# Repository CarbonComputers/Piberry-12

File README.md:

## PiBerry v12 – Final Iteration

**PiBerry v12** marks the final and most refined revision of the PiBerry handheld Linux terminal. Designed with both form and function in mind, this version brings together the best elements of previous iterations while introducing a more polished aesthetic, improved usability, and support for premium display hardware.

### 🔧 What's New in v12:

* **Refined Aesthetic Design**
  Complete overhaul of the external design for a cleaner, more modern look. Every detail has been revisited to ensure a visually cohesive and ergonomic form factor.
  Keyboard connectivity is simpler as it's driven via USB instead of I2C, you only have to flash the firmware and install the display drivers.

* **HyperPixel 4.0" Display Support**
  Now compatible with the high-resolution **HyperPixel 4.0" touchscreen**, offering a sharper, more responsive interface for your Linux workflows, tools, and custom interfaces, drivers are baked into Pi OS, and many others.
  Waveshare or other 3.5" displays are still compatible, make sure you use the right 3D file

* **Community & Collaboration**
  This final version wouldn’t have been possible without the support and insights of the amazing open-source and hardware community. Special thanks to all contributors, testers, and developers who offered feedback and improvements throughout the PiBerry journey.

### 🔍 Overview:

* Fully integrated handheld Linux device
* Designed around the Raspberry Pi Zero 2W (possibly a CM4 - with a mini carrier)
* Optimized for penetration testing, system diagnostics, portable dev environments, and retro computing/ gaming
* Runs your choice of Linux (Kali, Raspberry Pi OS, etc.)
* Powered by an onboard battery with safe shutdown and charging logic
* Support for keyboards, touch navigation, and peripheral integration with the BBQ20

---

PiBerry v12 is a culmination of passion, learning, and iteration — a celebration of community-powered hardware.

We hope you enjoy building and using it as much as we enjoyed bringing it to life.

Get yours or find out more about the latest builds at [Carbon Computers](https://carboncomputers.us)

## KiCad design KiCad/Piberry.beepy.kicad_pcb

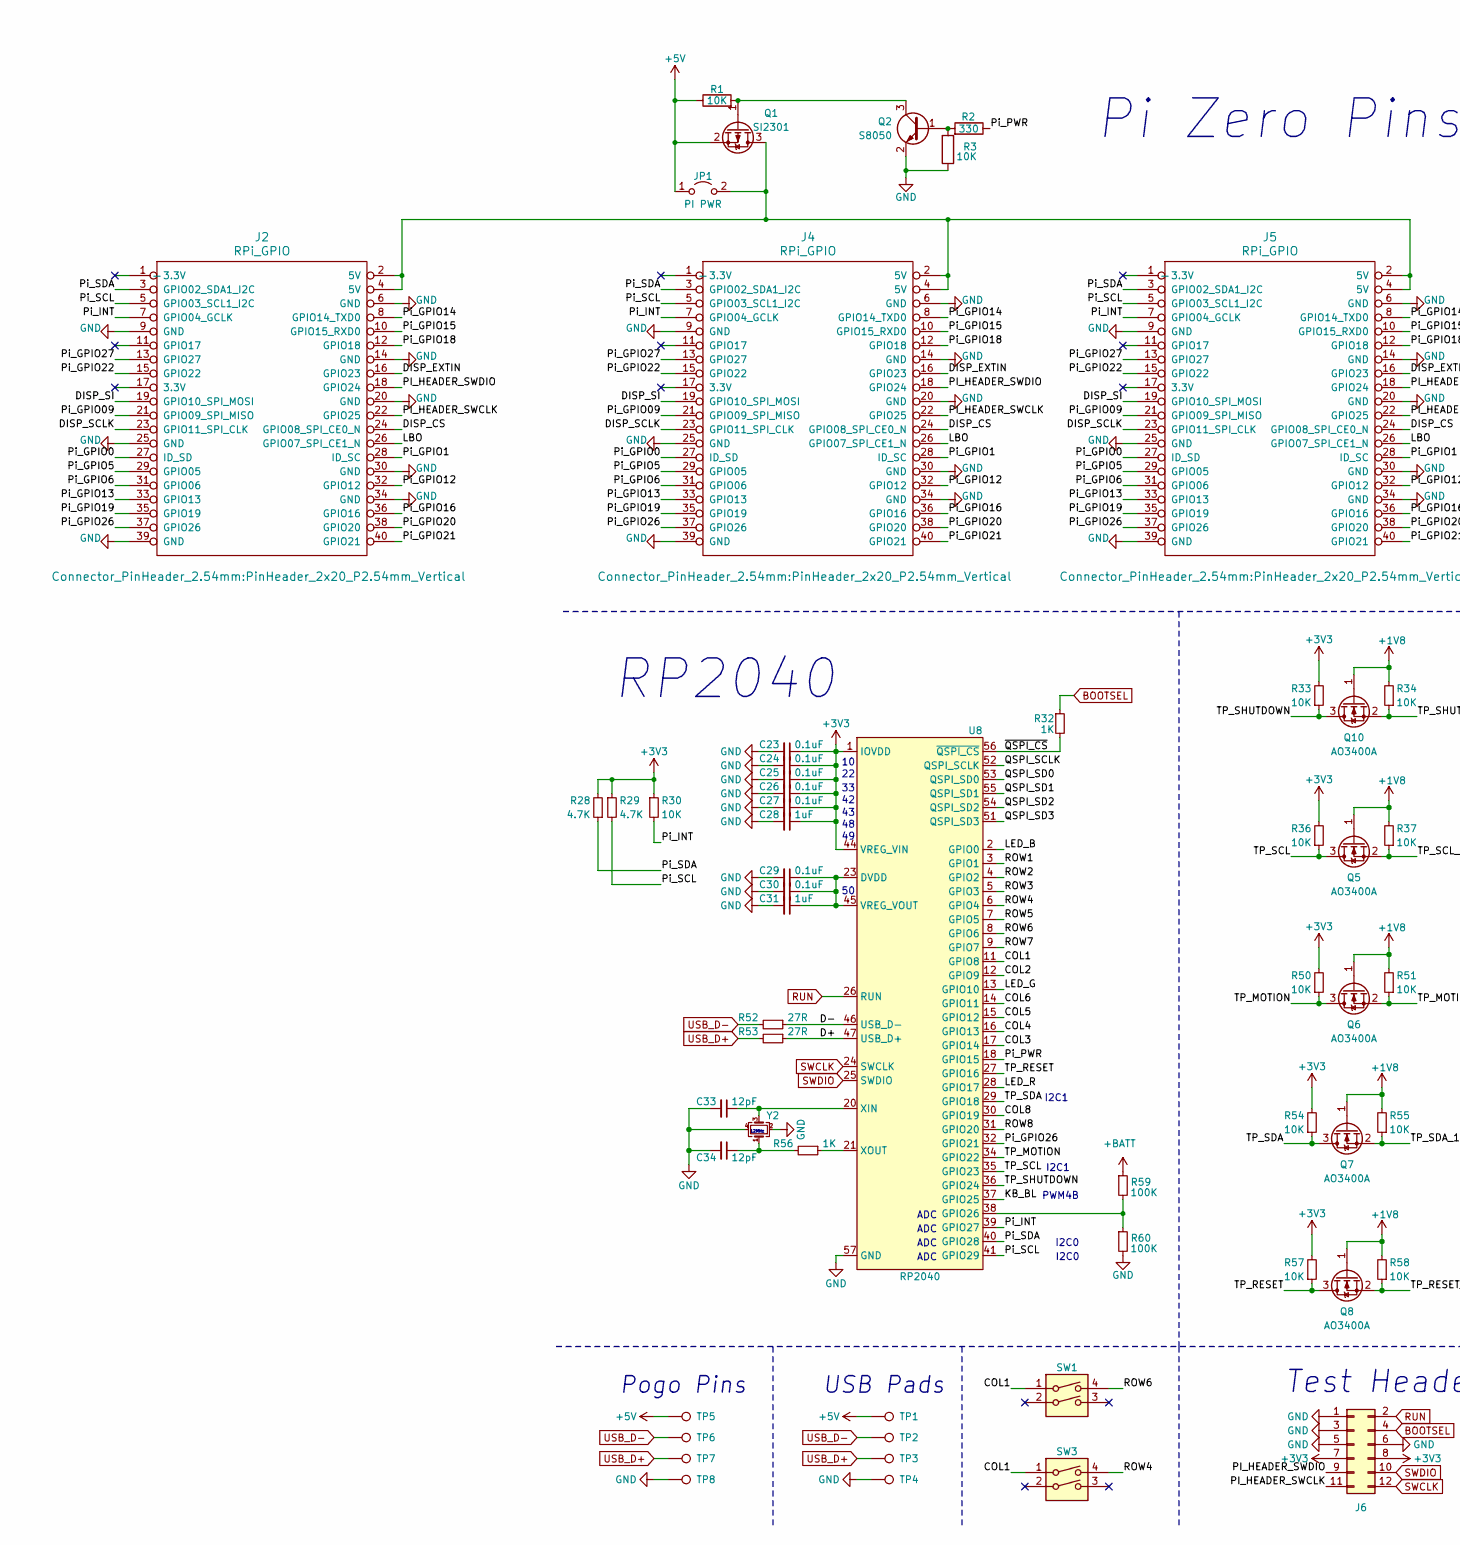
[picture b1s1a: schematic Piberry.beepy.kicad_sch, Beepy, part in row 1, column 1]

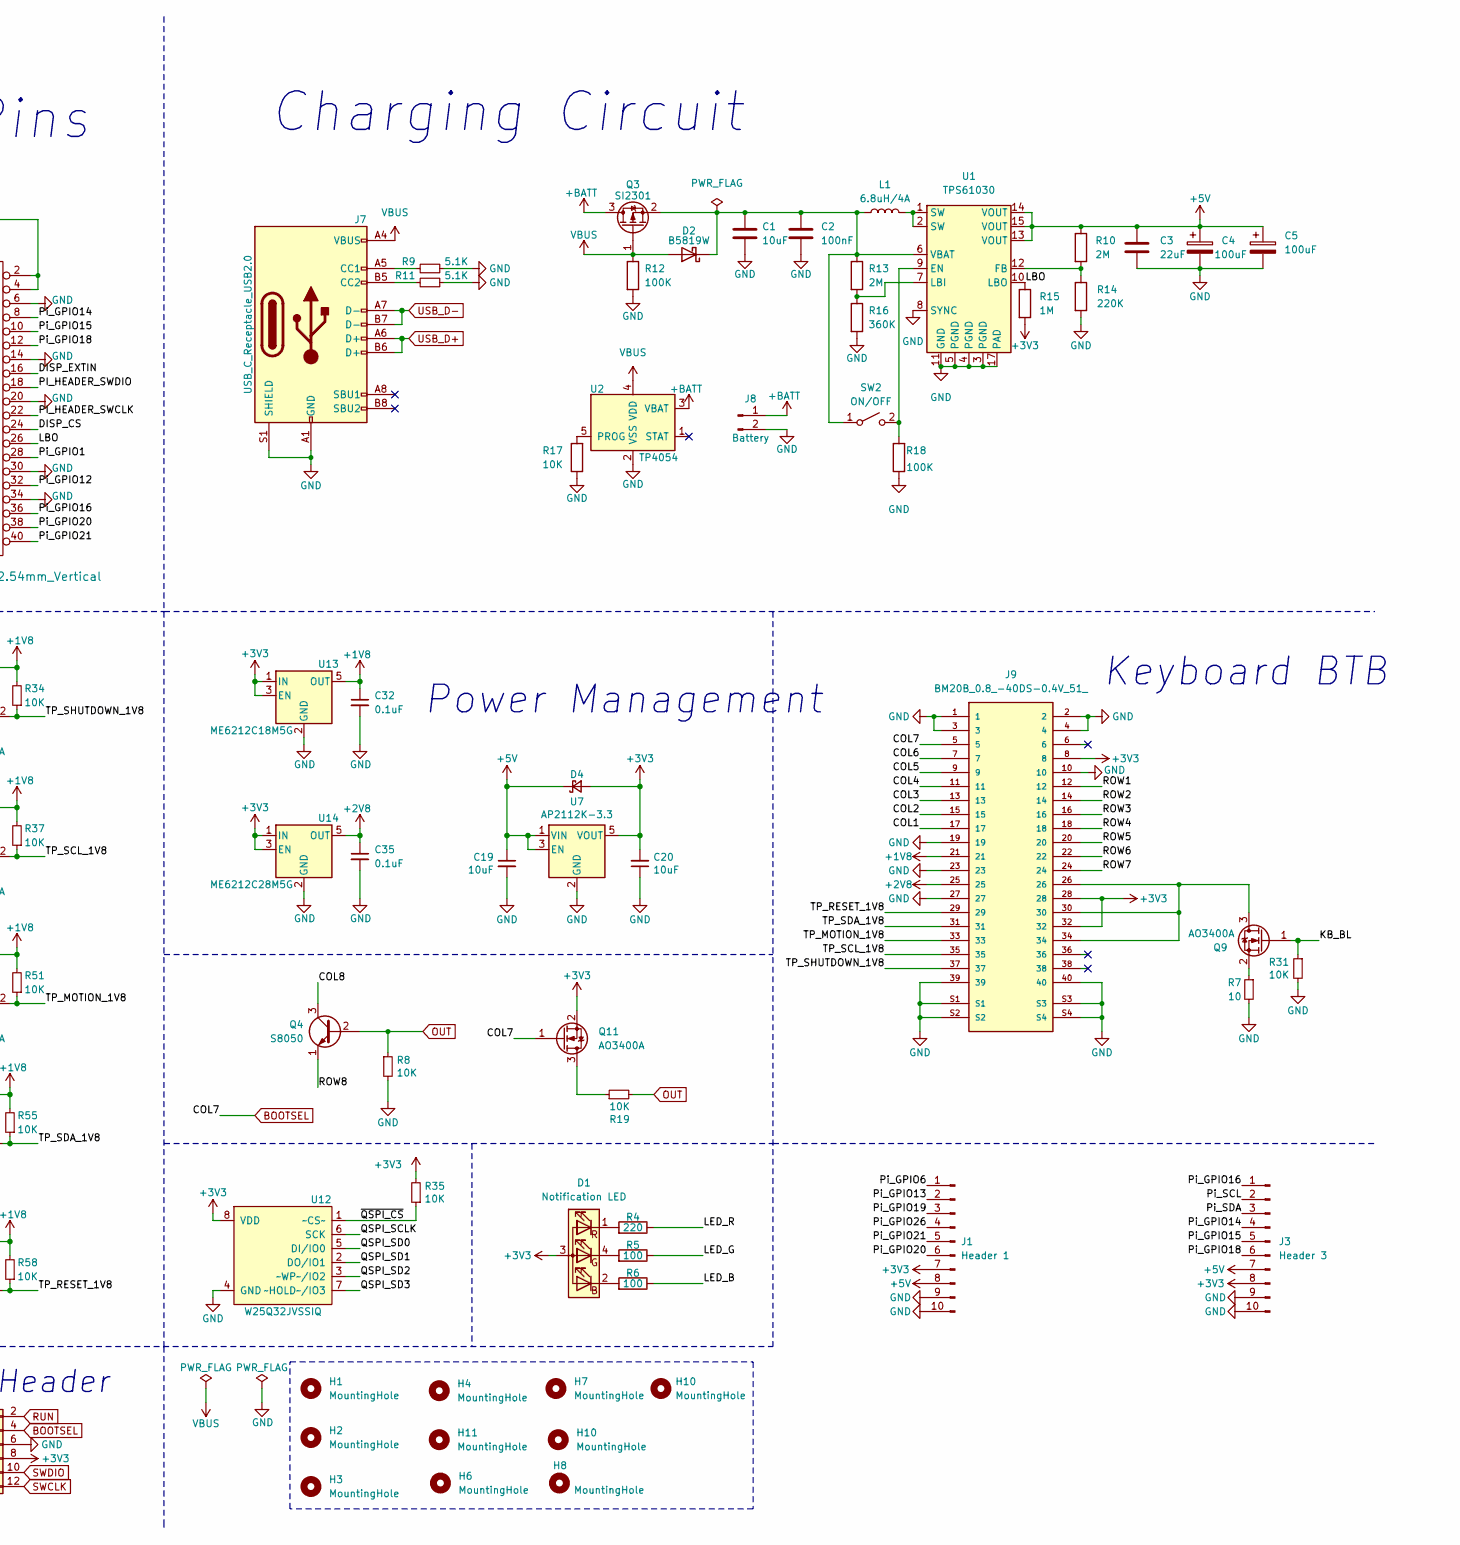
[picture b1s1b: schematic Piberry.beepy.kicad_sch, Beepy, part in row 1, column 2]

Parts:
C1, C19, C20: 10uF; C_0603_1608Metric; LCSC C96446
C2: 100nF; C_0603_1608Metric; LCSC C14663
C3: 22uF; C_1206_3216Metric; LCSC C12891
C4, C5: 100uF; CP_EIA-3528-15_AVX-H; LCSC C129289
C23, C24, C25, C26, C27, C29, C30, C32, C35: 0.1uF; C_0603_1608Metric; LCSC C14663
C28, C31: 1uF; C_0603_1608Metric; LCSC C15849
C33, C34: 12pF; C_0603_1608Metric; LCSC C38523
D1: Notification LED; FM-B2020RGBA-HG; LCSC C108793
D2: B5819W; D_SOD-123; LCSC C64885
D4: D_Schottky_Small; D_SOD-323; LCSC C114023
H1, H4, H7, H10: MountingHole; MountingHole_2.2mm_M2
H2, H3, H6, H11: MountingHole; MountingHole_2.5mm
H8: MountingHole; MountingHole_2.7mm_M2.5
J1: Header 1; PinHeader_1x10_P2.54mm_Vertical; LCSC C57369
J2, J4, J5: RPi_GPIO; PinHeader_2x20_P2.54mm_Vertical
J3: Header 3; PinHeader_1x10_P2.54mm_Vertical; LCSC C57369
J6: PRG_HEADER; PinHeader_2x06_P1.27mm_Vertical_SMD
J7: USB_C_Receptacle_USB2.0; USB_C_Receptacle_HRO_TYPE-C-31-M-12; LCSC C165948
J8: Battery; JST_PH_S2B-PH-SM4-TB_1x02-1MP_P2.00mm_Horizontal; LCSC C295747
J9: BM20B_0.8_-40DS-0.4V_51_; HRS_BM20B_0.8_-40DS-0.4V_51_; LCSC C424543
JP1: PI PWR; SolderJumper-2_P1.3mm_Open_RoundedPad1.0x1.5mm
L1: 6.8uH/4A; L_Bourns_SRP7028A_7.3x6.6mm; LCSC C497879
Q1, Q3: SI2301; SOT-23; LCSC C2891731
Q2, Q4: S8050; SOT-23; LCSC C916390
Q5, Q6, Q7, Q8, Q9, Q10, Q11: AO3400A; SOT-23; LCSC C20917
R1, R3, R8, R17, R19, R30, R31, R33, R34, R35, R36, R37, R50, R51, R54, R55, R57, R58: 10K; R_0603_1608Metric; LCSC C25804
R2: 330; R_0603_1608Metric; LCSC C23138
R4: 220; R_0603_1608Metric; LCSC C22962
R5, R6: 100; R_0603_1608Metric; LCSC C22775
R7: 10; R_0603_1608Metric; LCSC C22859
R9, R11: 5.1K; R_0603_1608Metric; LCSC C23186
R10, R13: 2M; R_0603_1608Metric; LCSC C22976
R12, R18, R59, R60: 100K; R_0603_1608Metric; LCSC C25803
R14: 220K; R_0603_1608Metric; LCSC C22961
R15: 1M; R_0603_1608Metric; LCSC C22935
R16: 360K; R_0603_1608Metric; LCSC C23146
R28, R29: 4.7K; R_0603_1608Metric; LCSC C23162
R32, R56: 1K; R_0603_1608Metric; LCSC C21190
R52, R53: 27R; R_0603_1608Metric; LCSC C403464
SW1, SW3: SW_DIP_x02; GT-TC018X; LCSC C963235
SW2: ON/OFF; SW_SPDT_PCM12; LCSC C963206
TP1, TP2, TP3, TP4: TestPoint; TestPoint_Pad_1.5x1.5mm
TP5, TP8: TestPoint; TestPoint_THTPad_D2.0mm_Drill1.0mm
TP6, TP7: TestPoint; TestPoint_THTPad_D1.5mm_Drill0.7mm
U1: TPS61030; HTSSOP-16-1EP_4.4x5mm_P0.65mm_EP3.4x5mm_Mask2.46x2.31mm_The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; LCSC C9842
U2: TP4054; SOT-23-5; LCSC C668215
U7: AP2112K-3.3; SOT-23-5; LCSC C51118
U8: RP2040; QFN-56-1EP_7x7mm_P0.4mm_EP5.6x5.6mm; LCSC C2040
U12: W25Q32JVSSIQ; SSOP-8_5.25x5.24mm_P1.27mm; LCSC C82344
U13: ME6212C18M5G; SOT-23-5; LCSC C236669
U14: ME6212C28M5G; SOT-23-5; LCSC C427596
Y2: XYDBPCNANF-12MHZ; Crystal_SMD_3225-4Pin_3.2x2.5mm; LCSC C284155

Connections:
+1V8: C32.1, J9.21, Q5.1 (G), Q6.1 (G), Q7.1 (G), Q8.1 (G), Q10.1 (G), R34.2, R37.2, R51.2, R55.2, R58.2, U13.5 (OUT)
+2V8: C35.1, J9.25, U14.5 (OUT)
+3V3: C20.2, C23.1, C24.1, C25.1, C26.1, C27.1, C28.1, D1.3 (A), D4.2 (A), J1.7, J3.8, J6.7, J6.8, J9.8, J9.28, J9.32, Q11.2 (S), R15.2, R28.2, R29.1, R30.1, R33.2, R35.2, R36.2, R50.2, R54.2, R57.2, U7.5 (VOUT), U8.1 (IOVDD), U8.10 (IOVDD), U8.22 (IOVDD), U8.33 (IOVDD), U8.42 (IOVDD), U8.43 (ADC_AVDD), U8.44 (VREG_VIN), U8.48 (USB_VDD), U8.49 (IOVDD), U12.8 (VDD), U13.1 (IN), U13.3 (EN), U14.1 (IN), U14.3 (EN)
+5V: C3.1, C4.1, C5.1, C19.1, D4.1 (K), J1.8, J3.7, JP1.1 (A), Q1.2 (S), R1.1, R10.1, TP1.1, TP5.1, U1.13 (VOUT), U1.14 (VOUT), U1.15 (VOUT), U7.1 (VIN), U7.3 (EN)
+BATT: J8.1, Q3.3 (D), R59.1, U2.3 (VBAT)
/COL1: J9.17, SW1.1, SW3.1, U8.11 (GPIO8)
/COL2: J9.15, U8.12 (GPIO9)
/COL3: J9.13, U8.17 (GPIO14)
/COL4: J9.11, U8.16 (GPIO13)
/COL5: J9.9, U8.15 (GPIO12)
/COL6: J9.7, U8.14 (GPIO11)
/COL8: Q4.3 (C), U8.30 (GPIO19)
/D+: R53.1, U8.47 (USB_D+)
/D-: R52.1, U8.46 (USB_D-)
/DISP_CS: J2.24 (GPIO08_SPI_CE0_N), J4.24 (GPIO08_SPI_CE0_N), J5.24 (GPIO08_SPI_CE0_N)
/DISP_EXTIN: J2.16 (GPIO23), J4.16 (GPIO23), J5.16 (GPIO23)
/DISP_SCLK: J2.23 (GPIO11_SPI_CLK), J4.23 (GPIO11_SPI_CLK), J5.23 (GPIO11_SPI_CLK)
/DISP_SI: J2.19 (GPIO10_SPI_MOSI), J4.19 (GPIO10_SPI_MOSI), J5.19 (GPIO10_SPI_MOSI)
/KB_BL: Q9.1 (G), R31.1, U8.37 (GPIO25)
/LBO: J2.26 (GPIO07_SPI_CE1_N), J4.26 (GPIO07_SPI_CE1_N), J5.26 (GPIO07_SPI_CE1_N), R15.1, U1.10 (LBO)
/LED_B: R6.1, U8.2 (GPIO0)
/LED_G: R5.1, U8.13 (GPIO10)
/LED_R: R4.1, U8.28 (GPIO17)
/PI_HEADER_SWCLK: J2.22 (GPIO25), J4.22 (GPIO25), J5.22 (GPIO25), J6.11
/PI_HEADER_SWDIO: J2.18 (GPIO24), J4.18 (GPIO24), J5.18 (GPIO24), J6.9
/Pi_GPIO0: J2.27 (ID_SD), J4.27 (ID_SD), J5.27 (ID_SD)
/Pi_GPIO1: J2.28 (ID_SC), J4.28 (ID_SC), J5.28 (ID_SC)
/Pi_GPIO5: J2.29 (GPIO05), J4.29 (GPIO05), J5.29 (GPIO05)
/Pi_GPIO6: J1.1, J2.31 (GPIO06), J4.31 (GPIO06), J5.31 (GPIO06)
/Pi_GPIO09: J2.21 (GPIO09_SPI_MISO), J4.21 (GPIO09_SPI_MISO), J5.21 (GPIO09_SPI_MISO)
/Pi_GPIO12: J2.32 (GPIO12), J4.32 (GPIO12), J5.32 (GPIO12)
/Pi_GPIO13: J1.2, J2.33 (GPIO13), J4.33 (GPIO13), J5.33 (GPIO13)
/Pi_GPIO14: J2.8 (GPIO14_TXD0), J3.4, J4.8 (GPIO14_TXD0), J5.8 (GPIO14_TXD0)
/Pi_GPIO15: J2.10 (GPIO15_RXD0), J3.5, J4.10 (GPIO15_RXD0), J5.10 (GPIO15_RXD0)
/Pi_GPIO16: J2.36 (GPIO16), J3.1, J4.36 (GPIO16), J5.36 (GPIO16)
/Pi_GPIO18: J2.12 (GPIO18), J3.6, J4.12 (GPIO18), J5.12 (GPIO18)
/Pi_GPIO19: J1.3, J2.35 (GPIO19), J4.35 (GPIO19), J5.35 (GPIO19)
/Pi_GPIO20: J1.6, J2.38 (GPIO20), J4.38 (GPIO20), J5.38 (GPIO20)
/Pi_GPIO21: J1.5, J2.40 (GPIO21), J4.40 (GPIO21), J5.40 (GPIO21)
/Pi_GPIO22: J2.15 (GPIO22), J4.15 (GPIO22), J5.15 (GPIO22)
/Pi_GPIO26: J1.4, J2.37 (GPIO26), J4.37 (GPIO26), J5.37 (GPIO26), U8.32 (GPIO21)
/Pi_GPIO27: J2.13 (GPIO27), J4.13 (GPIO27), J5.13 (GPIO27)
/Pi_INT: J2.7 (GPIO04_GCLK), J4.7 (GPIO04_GCLK), J5.7 (GPIO04_GCLK), R30.2, U8.39 (GPIO27)
/Pi_PWR: R2.1, U8.18 (GPIO15)
/Pi_SCL: J2.5 (GPIO03_SCL1_I2C), J3.2, J4.5 (GPIO03_SCL1_I2C), J5.5 (GPIO03_SCL1_I2C), R29.2, U8.41 (GPIO29)
/Pi_SDA: J2.3 (GPIO02_SDA1_I2C), J3.3, J4.3 (GPIO02_SDA1_I2C), J5.3 (GPIO02_SDA1_I2C), R28.1, U8.40 (GPIO28)
/QSPI_SCLK: U8.52 (QSPI_SCLK), U12.6 (SCK)
/QSPI_SD0: U8.53 (QSPI_SD0), U12.5 (DI/IO0)
/QSPI_SD1: U8.55 (QSPI_SD1), U12.2 (DO/IO1)
/QSPI_SD2: U8.54 (QSPI_SD2), U12.3 (~WP~/IO2)
/QSPI_SD3: U8.51 (QSPI_SD3), U12.7 (~HOLD~/IO3)
/ROW1: J9.12, U8.3 (GPIO1)
/ROW2: J9.14, U8.4 (GPIO2)
/ROW3: J9.16, U8.5 (GPIO3)
/ROW4: J9.18, SW3.4, U8.6 (GPIO4)
/ROW5: J9.20, U8.7 (GPIO5)
/ROW6: J9.22, SW1.4, U8.8 (GPIO6)
/ROW7: J9.24, U8.9 (GPIO7)
/ROW8: Q4.1 (E), U8.31 (GPIO20)
/TP_MOTION: Q6.3 (D), R50.1, U8.34 (GPIO22)
/TP_MOTION_1V8: J9.33, Q6.2 (S), R51.1
/TP_RESET: Q8.3 (D), R57.1, U8.27 (GPIO16)
/TP_RESET_1V8: J9.29, Q8.2 (S), R58.1
/TP_SCL: Q5.3 (D), R36.1, U8.35 (GPIO23)
/TP_SCL_1V8: J9.35, Q5.2 (S), R37.1
/TP_SDA: Q7.3 (D), R54.1, U8.29 (GPIO18)
/TP_SDA_1V8: J9.31, Q7.2 (S), R55.1
/TP_SHUTDOWN: Q10.3 (D), R33.1, U8.36 (GPIO24)
/TP_SHUTDOWN_1V8: J9.37, Q10.2 (S), R34.1
/~QSPI_CS: R32.2, R35.1, U8.56 (~QSPI_CS), U12.1 (~CS~)
BOOTSEL: J6.4, J9.5, Q11.1 (G), R32.1
GND: C1.2, C2.2, C3.2, C4.2, C5.2, C19.2, C20.1, C23.2, C24.2, C25.2, C26.2, C27.2, C28.2, C29.2, C30.2, C31.2, C32.2, C33.2, C34.2, C35.2, J1.9, J1.10, J2.6 (GND), J2.9 (GND), J2.14 (GND), J2.20 (GND), J2.25 (GND), J2.30 (GND), J2.34 (GND), J2.39 (GND), J3.9, J3.10, J4.6 (GND), J4.9 (GND), J4.14 (GND), J4.20 (GND), J4.25 (GND), J4.30 (GND), J4.34 (GND), J4.39 (GND), J5.6 (GND), J5.9 (GND), J5.14 (GND), J5.20 (GND), J5.25 (GND), J5.30 (GND), J5.34 (GND), J5.39 (GND), J6.1, J6.3, J6.5, J6.6, J7.A1 (GND), J7.A12 (GND), J7.B1 (GND), J7.B12 (GND), J7.S1 (SHIELD), J8.2, J9.1, J9.2, J9.3, J9.4, J9.10, J9.19, J9.23, J9.27, J9.39, J9.40, J9.S1, J9.S2, J9.S3, J9.S4, Q2.2 (E), R3.1, R7.2, R8.2, R9.1, R11.1, R12.2, R14.2, R16.2, R17.1, R18.1, R31.2, R60.2, TP4.1, TP8.1, U1.3 (PGND), U1.4 (PGND), U1.5 (PGND), U1.8 (SYNC), U1.11 (GND), U1.17 (PAD), U2.2 (VSS), U7.2 (GND), U8.19 (TESTEN), U8.57 (GND), U12.4 (GND), U12.9 (GND), U13.2 (GND), U14.2 (GND), Y2.2, Y2.4
unnamed: C34.1, R56.2, Y2.1
unnamed: D1.2 (BK), R6.2
unnamed: D1.4 (GK), R5.2
unnamed: D1.1 (RK), R4.2
unnamed: C1.1, C2.1, D2.1 (K), L1.1, Q3.2 (S), R13.1, SW2.1 (A), U1.6 (VBAT)
unnamed: J7.A5 (CC1), R9.2
unnamed: J7.B5 (CC2), R11.2
unnamed: J2.2 (5V), J2.4 (5V), J4.2 (5V), J4.4 (5V), J5.2 (5V), J5.4 (5V), JP1.2 (B), Q1.3 (D)
unnamed: L1.2, U1.1 (SW), U1.2 (SW)
unnamed: Q1.1 (G), Q2.3 (C), R1.2
unnamed: Q2.1 (B), R2.2, R3.2
unnamed: J9.26, J9.30, J9.34, Q9.3 (D)
unnamed: Q9.2 (S), R7.1
unnamed: Q11.3 (D), R19.1
unnamed: R18.2, SW2.2 (B), U1.9 (EN)
unnamed: R10.2, R14.1, U1.12 (FB)
unnamed: R13.2, R16.1, U1.7 (LBI)
unnamed: R17.2, U2.5 (PROG)
unnamed: R59.2, R60.1, U8.38 (GPIO26)
unnamed: C29.1, C30.1, C31.1, U8.23 (DVDD), U8.45 (VREG_VOUT), U8.50 (DVDD)
unnamed: C33.1, U8.20 (XIN), Y2.3
unnamed: R56.1, U8.21 (XOUT)
OUT: Q4.2 (B), R8.1, R19.2
RUN: J6.2, U8.26 (RUN)
SWCLK: J6.12, U8.24 (SWCLK)
SWDIO: J6.10, U8.25 (SWDIO)
USB_D+: J7.A6 (D+), J7.B6 (D+), R53.2, TP3.1, TP7.1
USB_D-: J7.A7 (D-), J7.B7 (D-), R52.2, TP2.1, TP6.1
VBUS: D2.2 (A), J7.A4 (VBUS), J7.A9 (VBUS), J7.B4 (VBUS), J7.B9 (VBUS), Q3.1 (G), R12.1, U2.4 (VDD)

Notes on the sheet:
RP2040
USB Pads
I2C1
ADC
Charging Circuit
I2C0
Pi Zero Pins
Test Header
Pogo Pins
PWM4B
Keyboard BTB
Power Management
12MHz

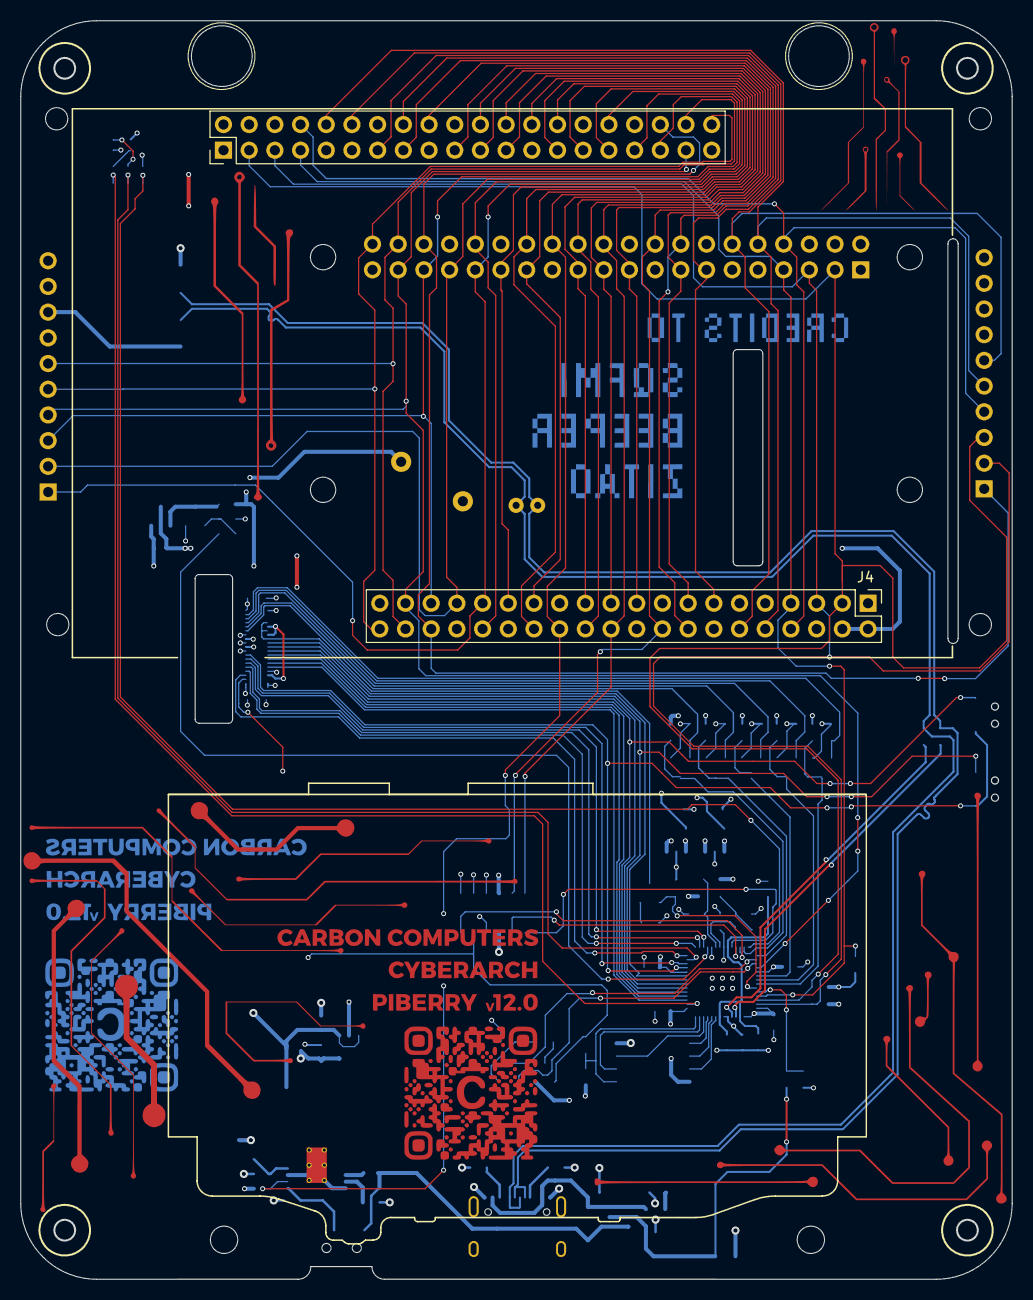
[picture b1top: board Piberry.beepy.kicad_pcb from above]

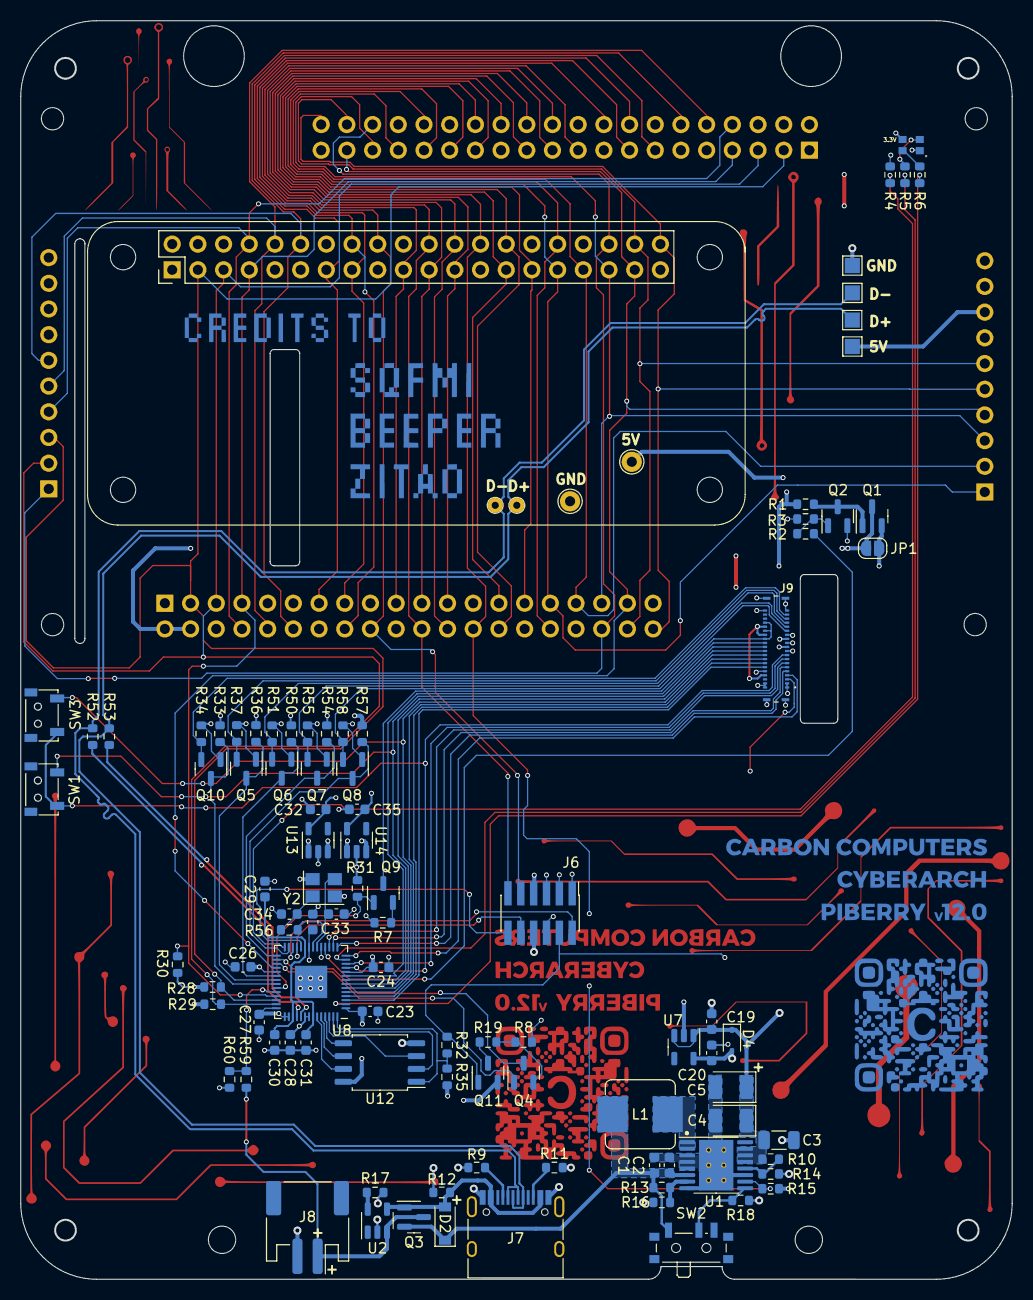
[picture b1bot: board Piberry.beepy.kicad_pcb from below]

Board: 4 copper layers, 98.0 x 124.4 mm, 114 parts (102 on the bottom side), 101 nets.

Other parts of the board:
H5, H9: MountingHole; MountingHole_2.5mm

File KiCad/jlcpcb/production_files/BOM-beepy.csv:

Comment,Designator,Footprint,LCSC
Notification LED,D1,FM-B2020RGBA-HG,C108793
D_Schottky_Small,D4,D_SOD-323,C114023
22uF,C3,C_1206_3216Metric,C12891
100uF,"C4,C5",CP_EIA-3528-15_AVX-H,C129289
100nF,"C2,C23,C24,C25,C26,C27,C29,C30,C32,C35",C_0603_1608Metric,C14663
1uF,"C28,C31",C_0603_1608Metric,C15849
USB_C_Receptacle_USB2.0,J7,USB_C_Receptacle_HRO_TYPE-C-31-M-12,C165948
RP2040,U8,QFN-56-1EP_7x7mm_P0.4mm_EP5.6x5.6mm,C2040
AO3400A,"Q10,Q11,Q5,Q6,Q7,Q8,Q9",SOT-23,C20917
1K,"R32,R56",R_0603_1608Metric,C21190
100,"R5,R6",R_0603_1608Metric,C22775
10,R7,R_0603_1608Metric,C22859
1M,R15,R_0603_1608Metric,C22935
220K,R14,R_0603_1608Metric,C22961
220,R4,R_0603_1608Metric,C22962
2M,"R10,R13",R_0603_1608Metric,C22976
330,R2,R_0603_1608Metric,C23138
360K,R16,R_0603_1608Metric,C23146
4.7K,"R28,R29",R_0603_1608Metric,C23162
5.1K,"R11,R9",R_0603_1608Metric,C23186
ME6212C18M5G,U13,SOT-23-5,C236669
100K,"R12,R18,R59,R60",R_0603_1608Metric,C25803
10K,"R1,R17,R19,R3,R30,R31,R33,R34,R35,R36,R37,R50,R51,R54,R55,R57,R58,R8",R_0603_1608Metric,C25804
XYDBPCNANF-12MHZ,Y2,Crystal_SMD_3225-4Pin_3.2x2.5mm,C284155
SI2301,"Q1,Q3",SOT-23,C2891731
Battery,J8,JST_PH_S2B-PH-SM4-TB_1x02-1MP_P2.00mm_Horizontal,C295747
12pF,"C33,C34",C_0603_1608Metric,C38523
27R,"R52,R53",R_0603_1608Metric,C403464
BM20B_0.8_-40DS-0.4V_51_,J9,HRS_BM20B_0.8_-40DS-0.4V_51_,C424543
ME6212C28M5G,U14,SOT-23-5,C427596
6.8uH/4A,L1,L_Bourns_SRP7028A_7.3x6.6mm,C497879
AP2112K-3.3,U7,SOT-23-5,C51118
Header 1,"J1,J3",PinHeader_1x10_P2.54mm_Vertical,C57369
B5819W,D2,D_SOD-123,C64885
TP4054,U2,SOT-23-5,C668215
W25Q32JVSSIQ,U12,SSOP-8_5.25x5.24mm_P1.27mm,C82344
S8050,"Q2,Q4",SOT-23,C916390
ON/OFF,SW2,SW_SPDT_PCM12,C963206
SW_DIP_x02,"SW1,SW3",GT-TC018X,C963235
10uF,"C1,C19,C20",C_0603_1608Metric,C96446
TPS61030,U1,HTSSOP-16-1EP_4.4x5mm_P0.65mm_EP3.4x5mm_Mask2.46x2.31mm_ThermalVias,C9842
RPi_GPIO,J2,PinHeader_2x20_P2.54mm_Vertical,

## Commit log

2025-07-16 Update README.md
    initial draft
2025-07-19 Initial commit
    adding product files
2025-07-19 updated read me
2025-07-19 updated link
2025-07-19 bbq20_firmware
    BBQ20 firmware

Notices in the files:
KiCad/Piberry.beepy.kicad_sch:
CERN Open Hardware Licence v1.2
